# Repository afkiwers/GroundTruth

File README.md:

> [!WARNING]
> **Vibe-coded, for illustrative purposes only.** GroundTruth was written largely with an AI assistant. Many of its
> results look reasonable, but they have not all been validated on real hardware: don't base design or compliance
> decisions on them alone.

# GroundTruth — return-path and EMI analysis for KiCad

GroundTruth finds where the return currents of fast signals and switching power stages really flow on a KiCad 10+
board, and what that does to emissions. It flags return-path problems (a trace crossing a plane split, a layer change
with no stitching via, a trace along a plane edge), solves the return current in every plane layer, and estimates how
much each detour adds to radiated and conducted emission, with fixes it checks before suggesting them.

On the same board model it also analyses:

- **DC-DC power stages and motor bridges**: hot loops, capacitor current sharing, switch-node overshoot, conducted
  emission through a LISN, losses, current density, control loops, and what the switching couples into the rest of the
  board ([Power stages](docs/guide/power.md));
- **temperatures**: copper and part temperatures from the currents and losses, and each stage's current capacity
  ([Thermal](docs/guide/power.md#temperatures-thermal-solve));
- **DC loads, power integrity, safety and signal integrity**: the drop each load sees, each IC's supply impedance,
  clearances and part ratings, impedance, skew and crosstalk ([Other analyses](docs/guide/analyses.md)).

It comes as a **KiCad plugin** (the window shown under [The plugin](#the-plugin), with heatmaps, markers drawn on the board and an HTML report) and
as the **`groundtruth` command line** for CI, which needs neither KiCad nor a display. Both use the same analysis core
and the same settings file, and give the same results.

## Install

**The KiCad plugin.** In KiCad, enable the API (**Preferences → Plugins → Enable KiCad API**, restart KiCad). Then
**Tools → Plugin and Content Manager → Manage… → Add** the repository
`https://afkiwers.github.io/GroundTruth/repository.json`, select it and install **GroundTruth**; new releases show up
as updates. Each [release](https://github.com/afkiwers/GroundTruth/releases) also has the package as a zip for
**Install from File…**. On the first start KiCad builds the plugin's Python environment (a few minutes); the button
**Analyse return paths** then appears in the PCB editor's top toolbar. The plugin has a fair few dependencies, so it can
take a couple of KiCad restarts before the buttons show.

**The command line.** Python 3.11 or newer; install a release's wheel (GroundTruth is not on PyPI):

```sh
pip install "groundtruth-pcb @ https://github.com/afkiwers/GroundTruth/releases/download/0.1.44625/groundtruth_pcb-0.1.44625-py3-none-any.whl"
```

More, including the development setup, GPU acceleration and where everything is on disk: [Installing](docs/guide/install.md).

**Optional speed-ups** (once per computer, KiCad closed; the installers are in the installed plugin's `tools`
folder): the **faster sparse solver** on Windows, `install_sparse.cmd` (Intel MKL PARDISO, ~250 MB; a Mac has Apple
Accelerate built in), and **GPU** support for an NVIDIA or AMD card, `install_gpu.py` / `install_gpu_amd.cmd`
(PyTorch, ~2.5 GB). Both only change the speed. Steps: [Installing, Optional speed-ups](docs/guide/install.md#optional-speed-ups).

## Quick start

In KiCad: open the board in the PCB editor and click **Analyse return paths**.

1. **Review** what GroundTruth found on the coloured tabs (orange rows): a net's driver and receivers and its timing,
   a converter's switches and operating point, a bridge's motor. Fill in what the board can't tell, press **Mark
   reviewed**.
2. **Run checks**: the rule checks; the Issues tab lists what they find.
3. **Simulate**: the field solver on everything ticked; the Results tab shows the maps and margins.
4. **Fix**: click an issue to see it in KiCad, let **Suggest fixes** propose vias and capacitors, try them as what-if
   edits.

The plugin folder has a demo board to try this on (`demo\README.txt`). On the command line:

```sh
groundtruth init board.kicad_pcb                 # the settings file, with every part's suggested model
groundtruth detect board.kicad_pcb --write       # nets, power stages and motor bridges to analyse (review them)
groundtruth check board.kicad_pcb                # the rule checks (seconds)
groundtruth simulate board.kicad_pcb --format html --out-dir report   # the field solver, an HTML report
```

## The plugin

**Getting there.** Once installed, GroundTruth puts two buttons at the right end of the PCB editor's top toolbar (red
box above). They are two separate actions, so each has its own button:

- **Analyse return paths** (the right one, the ground symbol) opens the GroundTruth window for the board open in the
  PCB editor. This is where everything happens: setup, Run checks, Simulate, results and issues.
- **Add selected net to GroundTruth** (the left one, with the green plus) adds a net you pick on the board to the
  window's **Signal paths** tab, so you don't need to find it in a list:
  1. In the PCB editor, select a track, via or pad of the net (click it; a right-click selects it too).
  2. Press the button. The net is added as a new signal path, and the GroundTruth window comes to the front. If no
     window is open for the board, one opens and adds the net once it has read the board.
  3. GroundTruth suggests the driver and receiver pins from the pin types. Check the row, which is orange until you
     review it; set the frequency and rise time if the net's name matches no signal class.

  To add a **whole path through several nets** (for example a current-sense amplifier → op-amp → microcontroller
  ADC), Ctrl+click one bit of copper on each net, then press the button once. GroundTruth puts the nets in order
  through the parts joining them and adds one signal path, with the series resistors as pass-through parts and the
  op-amp modelled as an amplifier. Ground, supply and power-stage nets (switch node, inductor output) are refused
  with the reason. KiCad 10 doesn't let plugins add entries to the right-click menu, hence the toolbar button.

A third action, **Clear GT markers**, removes the markers, contours and arrows GroundTruth drew on the board. It has no
toolbar button: find it under **Tools → External Plugins**, or in the window's top bar.

**Set up.** The coloured tabs are what a run analyses: signal paths, converters, motor bridges, DC loads, power
integrity rails and signal-integrity pairs, each row with a tick box. GroundTruth detects them when a board is opened
(orange until you review them); each tab's badge counts the rows the next run takes. **Run checks** gives the rule
checks in seconds, **Simulate** the field solver in minutes. **Configuration ▾** saves and loads a set-up, **Undo**
takes back a change.

**Results.** The return current in each plane layer as a heatmap with current arrows, and the vias that carry it
between layers. **Markers ▾** picks what is drawn over the map, **Draw on board ▾** puts the contours, the arrows or the
hot loop into KiCad, **Open 3D view** opens the board in your browser, and **Further analysis ▾** adds the thermal
solve, the current capacity of a stage and a sharper (finer) map.

A **power stage** gets its own views: here a buck's hot loop in two layers, with the busiest via, the loop inductance,
the switch-node ringing, the input capacitors' share and the radiated and conducted margins in the tiles above it.

Scrolling down, the **cross-section** shows each plane layer's share of the return current along the route (red:
carrying the return, blue: flowing the other way) and the **emission spectrum** against its limit.

**Issues.** Every finding with its severity; a click selects, highlights and zooms to it in KiCad.

**Fixes** proposes stitching vias and capacitors for a route, and **design changes** for a power stage: a slower
switch-node edge, a snubber, an input filter, a common-mode budget. Each is predicted, then verified by running the
whole analysis again on a copy of the board, with its margins, overshoot and extra loss, the parts to buy and a
circuit (here an input π-filter and its corner frequency). **History** keeps every Simulate to compare; **Export
report…** writes the results as one HTML page. The plugin's own **Help** (F1) explains each tab.

## Part parameters for your parts database

GroundTruth reads part parameters (a FET's `Rds(on)` and `Coss`, a capacitor's `ESR` and `Cbias`, an op-amp's `GBW`,
a controller's `Vref` …) from the symbols' fields. Add them to the parts in your parts database, and KiCad's HTTP
library interface brings them into the schematic with the parts, where GroundTruth reads them on every run. The full
list, grouped by the tab that uses each (a parameter used on several tabs is listed under each, with where else it is
used): [Part parameters](docs/guide/part-fields.md).

## Documentation

| Guide | What's in it |
|---|---|
| [Installing](docs/guide/install.md) | the plugin and the command line, the development setup, GPU acceleration, where things are |
| [How it works](docs/guide/how-it-works.md) | the analyses, how the solver splits the work, accuracy and what the numbers mean |
| [Part parameters](docs/guide/part-fields.md) | every part parameter GroundTruth reads from the symbols' fields, by tab: to add to your parts database |
| [The settings file](docs/guide/settings.md) | what a board's settings hold, configurations, part models from the schematic, the checks and their severities, finding the nets, GT labels |
| [Working in KiCad](docs/guide/plugin.md) | showing issues on the board, drawing on it, fix suggestions and what-if edits |
| [Power stages and bridges](docs/guide/power.md) | DC-DC converters, motor bridges, victims, control loops, the thermal solve |
| [Other analyses](docs/guide/analyses.md) | op-amp circuits and Bode plots, capacitance at DC bias, DC loads, power integrity, safety checks, signal integrity |
| [The command line](docs/guide/cli.md) | the commands, options and exit codes |
| [CI (GitLab)](docs/guide/ci.md) | checking a board repository in a pipeline, the release gate `groundtruth verify` and its thresholds |
| [Compute server](docs/guide/compute-server.md) | running the heavy analyses on other machines on the network |
| [Status and roadmap](docs/guide/status.md) | what is done and what is planned |
| [Releases](docs/guide/releases.md) | for maintainers: how a release is built, signed and published |

For developers: [Development](docs/guide/development.md) (the source tree), [ARCHITECTURE.md](docs/ARCHITECTURE.md)
(the physics, data flow and design decisions) and [REFERENCES.md](docs/REFERENCES.md) (every source and assumption).
Example boards with their settings: [examples/](examples/README.md).

## License

GroundTruth is free software under the GNU General Public License v3.0: see [LICENSE](LICENSE).

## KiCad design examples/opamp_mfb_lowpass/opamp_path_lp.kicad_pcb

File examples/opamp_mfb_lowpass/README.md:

# Multiple-feedback low-pass (drawn in KiCad)

A 2nd-order multiple-feedback low-pass around an OPA376, the design of TI's OPA376 datasheet (SBOS406G, §8.2,
"Typical Application"): R1 590 Ω, R3 499 Ω, R4 2.94 kΩ, C2 39 nF, C5 1 nF; inverting gain 5, 25 kHz cutoff, a
Chebyshev response with 3 dB of peaking. Unlike the other examples it is a real KiCad project (schematic and board),
not generated, and it is the reference for `tests/test_example_mfb.py`.

    groundtruth bode examples/opamp_mfb_lowpass/opamp_path_lp.kicad_pcb --to 1MHz

GroundTruth reads the circuit from the board and finds the path J1.2 → R1 → R3 → U1 → J2.2 (the op-amp recognised by
its pin names; its + input on GND, so the signal enters at the − input). Its ideal transfer function, in the parts'
names, is exactly TI's Eq. 1:

    H(s) = −1/(R1·R3·C2·C5) / (s² + (s/C2)·(1/R1 + 1/R3 + 1/R4) + 1/(R3·R4·C2·C5))

DC gain −R4/R1 = −4.98, f0 = 1/(2π·√(R3·R4·C2·C5)) = 21.0 kHz. With the board's tracks and the op-amp's macromodel
the Bode plot shows +13.6 dB (4.78×), 2.9 dB of peaking at 17 kHz and −3 dB at 28 kHz: the gain is 4.78, not 4.98,
because the settings give the source 25 Ω (`analysis.driver_ohms`), in series with R1 (2940 / 615).

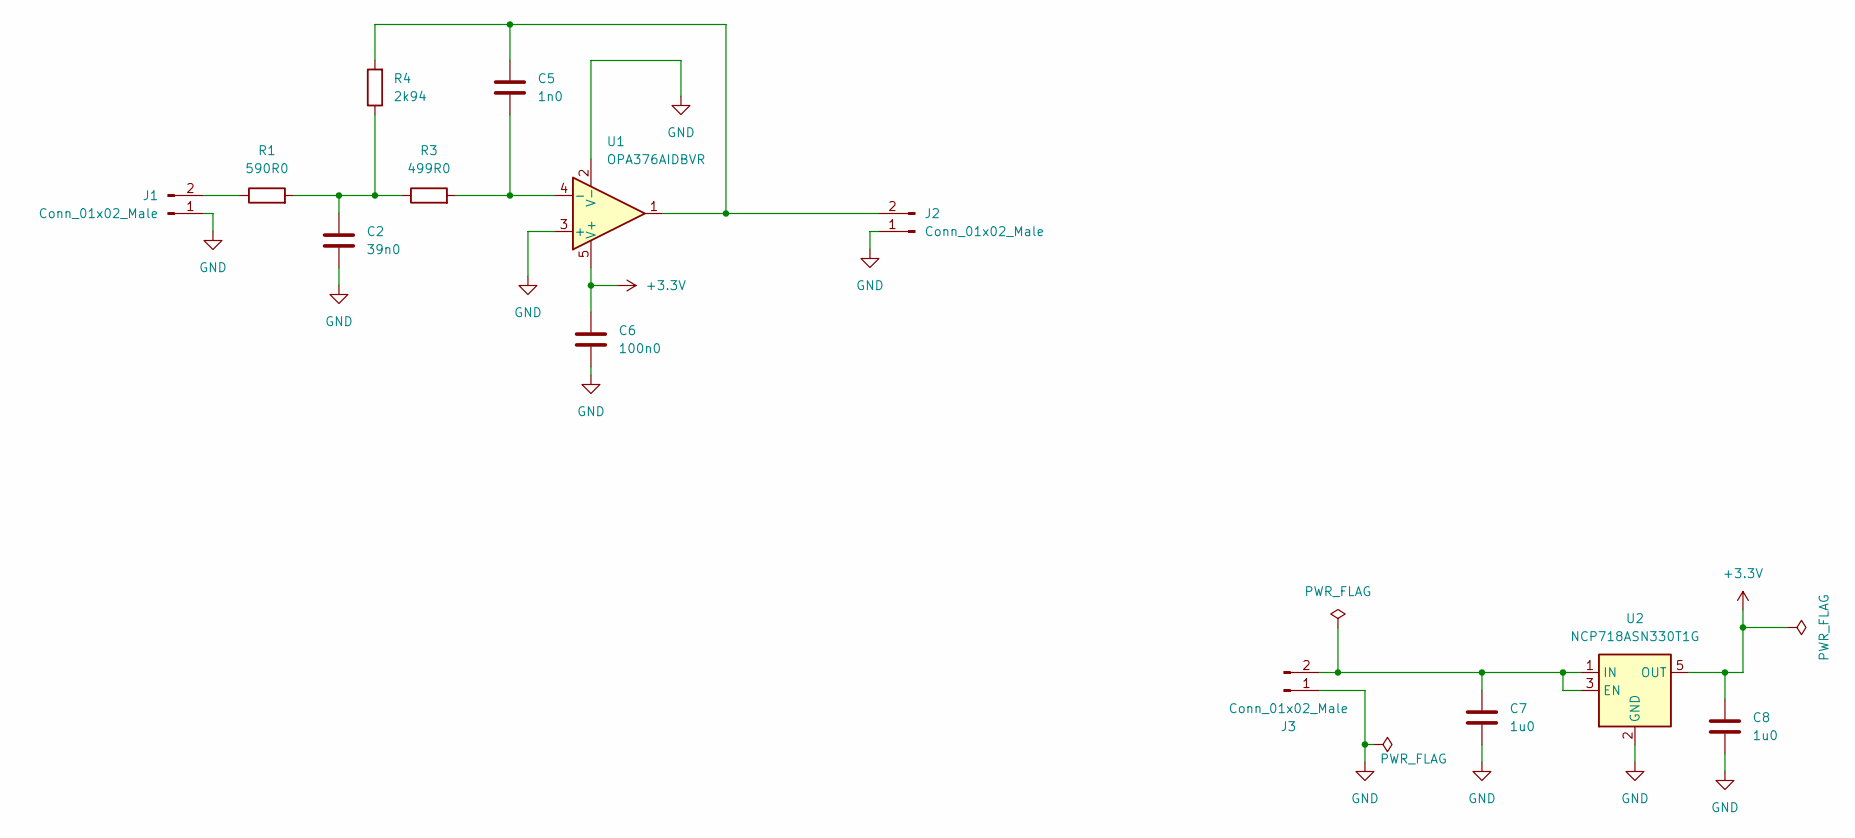
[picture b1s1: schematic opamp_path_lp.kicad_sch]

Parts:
C2: 39n0; C_0603_1608Metric; Rated Voltage 50V; Tolerance 10%
C5: 1n0; C_0402_1005Metric_RoundPaste; Rated Voltage 100V; Tolerance 5%
C6: 100n0; C_0603_1608Metric_HomePlatePaste; Rated Voltage 50V; Tolerance 10%
C7, C8: 1u0; C_0805_2012Metric; Rated Voltage 10V; Tolerance 10%
J1, J2, J3: Conn_01x02_Male; Hirose_DF57H-2P-1.2V_1x02_P1.2mm_Socket
R1: 590R0; R_0603_1608Metric
R3: 499R0; R_0603_1608Metric
R4: 2k94; R_0603_1608Metric
U1: OPA376AIDBVR; SOT-23-5; Rated Voltage 5.5V
U2: NCP718ASN330T1G; SOT-23-5

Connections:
+3.3V: C6.1, C8.1, U1.5 (V+), U2.5 (OUT)
GND: C2.2, C6.2, C7.2, C8.2, J1.1, J2.1, J3.1, U1.2 (V-), U1.3 (+), U2.2 (GND)
unnamed: C2.1, R1.2, R3.1, R4.1
unnamed: J1.2, R1.1
unnamed: C5.2, J2.2, R4.2, U1.1
unnamed: C7.1, J3.2, U2.1 (IN), U2.3 (EN)
unnamed: C5.1, R3.2, U1.4 (-)

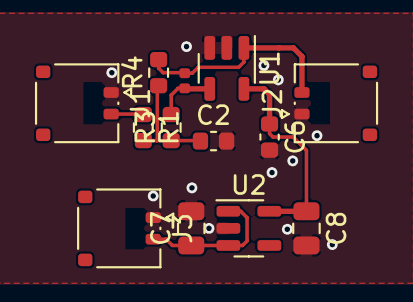
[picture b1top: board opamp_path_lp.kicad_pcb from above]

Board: 2 copper layers, 13 parts (0 on the bottom side), 7 nets.

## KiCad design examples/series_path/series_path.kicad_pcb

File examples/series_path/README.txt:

series_path
===========

A signal path across four nets: U1 → 33 Ω R1 → 1 µH L1 → 100 nF C1 (an AC-coupling capacitor, named in the net's Pass through) → U2. Each part's impedance counts at its place; the inductor resonates with the load near 60 MHz and blocks the current above.

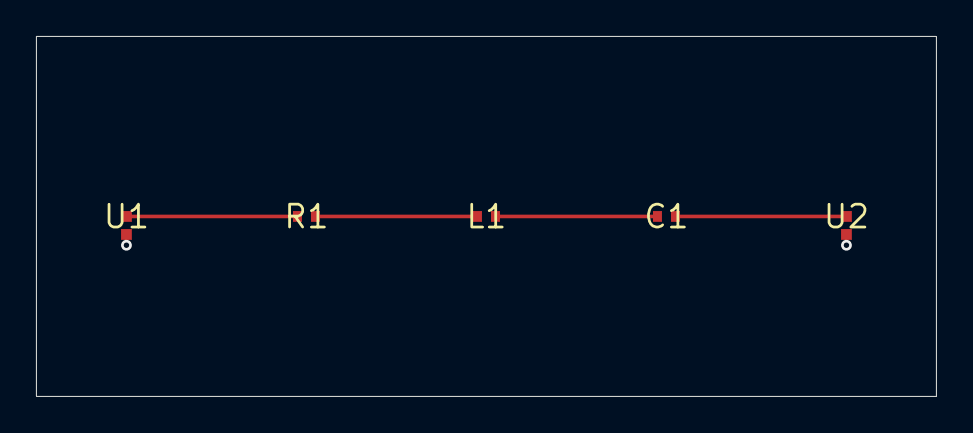
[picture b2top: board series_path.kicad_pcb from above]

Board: 2 copper layers, 50.0 x 20.0 mm, 5 parts (0 on the bottom side), 5 nets.

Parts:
C1: 100n; C_0402_1005Metric
L1: 1u; R_0402_1005Metric
R1: 33; R_0402_1005Metric
U1, U2: IC; Fake_IC

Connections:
GND: U1.2 (GND_2), U2.2 (GND_2)
SIG_A: R1.1, U1.1
SIG_B: L1.1, R1.2
SIG_C: C1.1, L1.2
SIG_D: C1.2, U2.1

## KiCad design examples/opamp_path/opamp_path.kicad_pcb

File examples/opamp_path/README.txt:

opamp_path
==========

A signal path through an op-amp stage: U1 → 33 Ω R1 → op-amp U5 (Gain 10, GBW 10 MHz from its symbol fields) → U2. Two current loops, both returning at U5's GND pin; the report's signal path lists the op-amp with its gain at the worst harmonic.

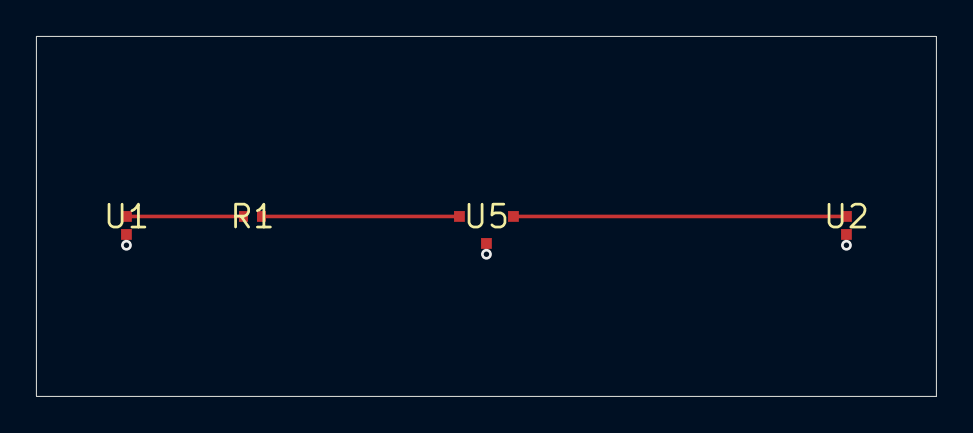
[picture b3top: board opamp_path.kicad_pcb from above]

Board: 2 copper layers, 50.0 x 20.0 mm, 4 parts (0 on the bottom side), 4 nets.

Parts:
R1: 33; R_0402_1005Metric
U1, U2: IC; Fake_IC
U5: OPA376; SOT-23-5

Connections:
GND: U1.2 (GND_2), U2.2 (GND_2), U5.2 (GND)
SIG_A: R1.1, U1.1
SIG_B: R1.2, U5.3 (+IN)
SIG_C: U2.1, U5.1 (OUT)

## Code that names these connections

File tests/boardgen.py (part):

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    y = 10.0
    g.ic("U1", (5.0, y), "SIG_A", gnd_offset=(0.0, 1.0))
    g.ic("U2", (35.0, y), "SIG_B", gnd_offset=(0.0, 1.0))
    g.two_pin("R1", r, (15.0, y), "SIG_A", "SIG_B", kind="R")
    g.track((5.0, y), (14.5, y), "SIG_A")
    g.track((15.5, y), (35.0, y), "SIG_B")
    g.two_pin("C9", c, (25.0, y + 2.0), "SIG_B", "GND", kind="C")
    g.track((24.5, y), (24.5, y + 2.0), "SIG_B")
    g.plane("GND", g.cu[-1])
    for x, yy in ((5.0, y + 1.0), (35.0, y + 1.0), (25.5, y + 2.0)):
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

def opamp_path_board(r_after: Optional[str] = None, **fields: str) -> BoardGen:
    """A signal path through an op-amp stage over a GND plane: U1.1 (SIG_A) → R1 33 Ω → SIG_B → U5 (+IN pin 3,
    OUT pin 1, GND pin 2 with a via to the plane) → SIG_C → U2.1. `fields`: U5's symbol fields as an HTTP lib would
    give them (Gain="10", GBW="10MHz" ...); a Gain field makes U5 an amplifier. r_after: a resistor R2 of this
    value between U5's output and U2 (SIG_C → R2 → SIG_D → U2.1), as refboard's R41 after the buffer."""
    g = BoardGen(layers=2, size=(50.0, 20.0))
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    last = "SIG_D" if r_after else "SIG_C"
    g.ic("U1", (5.0, y), "SIG_A", gnd_offset=(0.0, 1.0))
    g.ic("U2", (45.0, y), last, gnd_offset=(0.0, 1.0))
    g.two_pin("R1", "33", (12.0, y), "SIG_A", "SIG_B", kind="R")
    if r_after:
        g.two_pin("R2", r_after, (38.5, y), "SIG_C", "SIG_D", kind="R")
    g.footprint("U5", "OPA376", "Package_TO_SOT_SMD:SOT-23-5", (25.0, y), [
        {"number": 3, "at": (-1.5, 0.0), "net": "SIG_B", "pintype": "input", "pinfunction": "+IN"},
        {"number": 1, "at": (1.5, 0.0), "net": "SIG_C", "pintype": "output", "pinfunction": "OUT"},
        {"number": 2, "at": (0.0, 1.5), "net": "GND", "pintype": "power_in", "pinfunction": "GND"},
    ])
    if fields:
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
